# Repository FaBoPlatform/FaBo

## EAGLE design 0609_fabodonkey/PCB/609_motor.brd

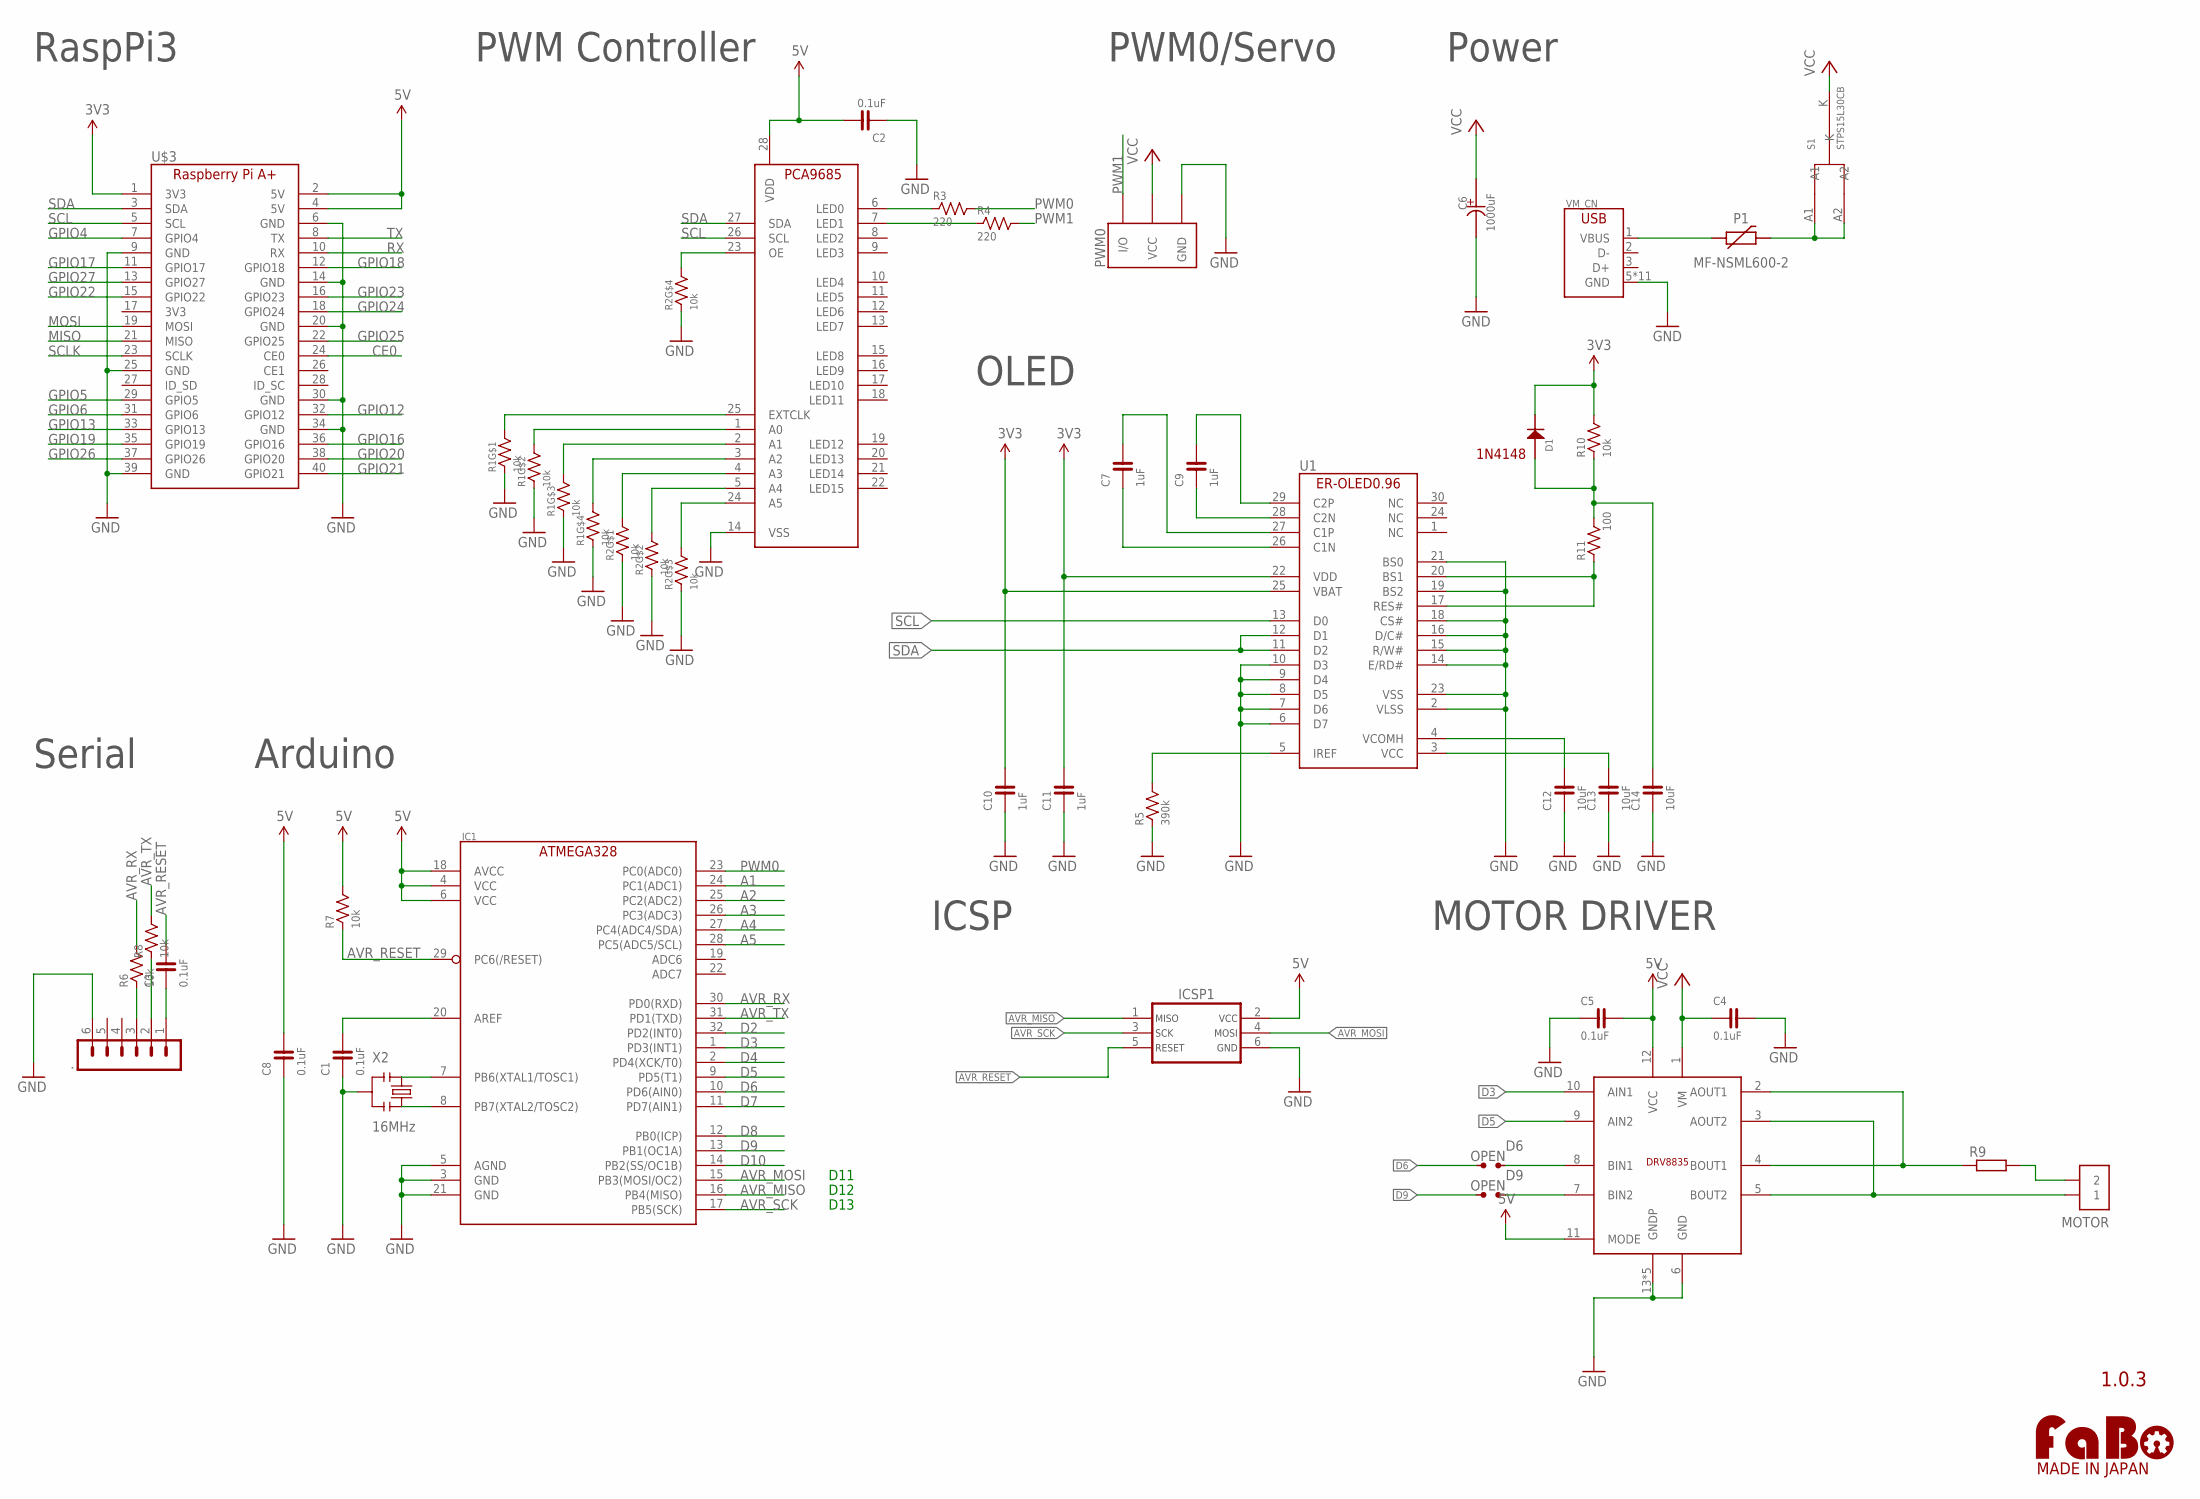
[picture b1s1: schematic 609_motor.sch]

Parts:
.: MA06-1
C1, C2, C3, C4, C5, C8: 0.1uF; 0603
C6: 1000uF; D12.5
C7, C9, C10, C11: 1uF; 0603
C12, C13, C14: 10uF; 0603
D1: 1N4148; 1N4148W
D6, D9: OPEN; SMD-JUMPER-2-OPEN
IC1: ATMEGA328P-AU; TQFP-32
ICSP1: ICSP_AVR-TC_NOHOLE; TC2030
M1: DRV8835
MOTOR: PIN_HEADER_1X2WIDE-WIDTH; PIN_1X2_WIDE_WIDTH
P1: MF-NSML600-2; 1206
PWM0: FABO_BRICK_3PIN-HEADER; FABO_BRICK_3PIN_HEADER
R1, R2: 10k; EXBV8V
R3, R4: 220; 0603
R5: 390k; 0603
R6, R7, R8, R10: 10k; 0603
R9: R-EU_0922/22; 0922/22
R11: 100; 0603
S1: STPS15L30CB; STPS15L30C
U1: ER-OLED0.96-1ER-CON30HT-1; ER-CON30HT-1
U$3: RASPBERRY_PI_A+
U$9: PCA9685
U$14: LOGO_FABO-M; LOGO_FABO_MS
VM_CN: USB-ZX62D; ZX62D-B-5PA8
X2: 16MHz; CSTNE_V_C

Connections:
3V3: C10.2, C11.2, D1.CATHODE, R10.2, U1.22 (VDD), U1.25 (VBAT), U$3.1 (3V3)
5V: C2.2, C5.2, C8.2, IC1.4 (VCC), IC1.6 (VCC), IC1.18 (AVCC), ICSP1.2, M1.11 (MODE), M1.12 (VCC), R7.2, U$3.2 (5V), U$3.4 (5V), U$9.28 (VDD)
A1: IC1.24 (PC1(ADC1))
A2: IC1.25 (PC2(ADC2))
A3: IC1.26 (PC3(ADC3))
A4: IC1.27 (PC4(ADC4/SDA))
A5: IC1.28 (PC5(ADC5/SCL))
AVR_MISO: IC1.16 (PB4(MISO)), ICSP1.1
AVR_MOSI: IC1.15 (PB3(MOSI/OC2)), ICSP1.4
AVR_RESET: C3.2, IC1.29 (PC6(/RESET)), ICSP1.5, R7.1
AVR_RX: IC1.30 (PD0(RXD)), R6.2
AVR_SCK: IC1.17 (PB5(SCK)), ICSP1.3
AVR_TX: IC1.31 (PD1(TXD)), R8.2
CE0: U$3.24 (CE0)
D2: IC1.32 (PD2(INT0))
D3: IC1.1 (PD3(INT1)), M1.10 (AIN1)
D4: IC1.2 (PD4(XCK/T0))
D5: IC1.9 (PD5(T1)), M1.9 (AIN2)
D6: D6.1, IC1.10 (PD6(AIN0))
D7: IC1.11 (PD7(AIN1))
D8: IC1.12 (PB0(ICP))
D9: D9.1, IC1.13 (PB1(OC1A))
D10: IC1.14 (PB2(SS/OC1B))
GND: ..6, C1.1, C2.1, C4.2, C5.1, C6.-, C8.1, C10.1, C11.1, C12.1, C13.1, C14.1, IC1.3 (GND), IC1.5 (AGND), IC1.21 (GND), ICSP1.6, M1.6 (GND), M1.13 (GNDP), M1.14 (GNDP), M1.15 (GNDP), M1.16 (GNDP), M1.17 (GNDP), PWM0.GND, R1.1, R1.2 (1), R1.3 (1), R1.4 (1), R2.1, R2.2 (1), R2.3 (1), R2.4 (1), R5.1, U1.2 (VLSS), U1.6 (D7), U1.7 (D6), U1.8 (D5), U1.9 (D4), U1.10 (D3), U1.14 (E/RD#), U1.15 (R/W#), U1.16 (D/C#), U1.18 (CS#), U1.19 (BS2), U1.21 (BS0), U1.23 (VSS), U$3.6 (GND), U$3.9 (GND), U$3.14 (GND), U$3.20 (GND), U$3.25 (GND), U$3.30 (GND), U$3.34 (GND), U$3.39 (GND), U$9.14 (VSS), VM_CN.5 (GND), VM_CN.B1 (GND), VM_CN.B2 (GND), VM_CN.B3 (GND), VM_CN.B4 (GND), VM_CN.T1 (GND), VM_CN.T2 (GND), VM_CN.T3 (GND), VM_CN.T4 (GND), VM_CN.T5 (GND), VM_CN.T6 (GND), X2.2
GPIO4: U$3.7 (GPIO4)
GPIO5: U$3.29 (GPIO5)
GPIO6: U$3.31 (GPIO6)
GPIO12: U$3.32 (GPIO12)
GPIO13: U$3.33 (GPIO13)
GPIO16: U$3.36 (GPIO16)
GPIO17: U$3.11 (GPIO17)
GPIO18: U$3.12 (GPIO18)
GPIO19: U$3.35 (GPIO19)
GPIO20: U$3.38 (GPIO20)
GPIO21: U$3.40 (GPIO21)
GPIO22: U$3.15 (GPIO22)
GPIO23: U$3.16 (GPIO23)
GPIO24: U$3.18 (GPIO24)
GPIO25: U$3.22 (GPIO25)
GPIO26: U$3.37 (GPIO26)
GPIO27: U$3.13 (GPIO27)
LED0: R3.1, U$9.6 (LED0)
LED1: R4.1, U$9.7 (LED1)
MISO: U$3.21 (MISO)
MOSI: U$3.19 (MOSI)
unnamed: C7.2, U1.27 (C1P)
unnamed: D6.2, M1.8 (BIN1)
unnamed: ..3, R6.1
unnamed: IC1.8 (PB7(XTAL2/TOSC2)), X2.3
unnamed: ..2, R8.1
unnamed: R2.5 (2), U$9.23 (OE)
unnamed: R1.8 (2), U$9.25 (EXTCLK)
unnamed: R1.7 (2), U$9.1 (A0)
unnamed: R1.6 (2), U$9.2 (A1)
unnamed: R1.5 (2), U$9.3 (A2)
unnamed: R2.8 (2), U$9.4 (A3)
unnamed: R2.7 (2), U$9.5 (A4)
unnamed: R2.6 (2), U$9.24 (A5)
unnamed: IC1.7 (PB6(XTAL1/TOSC1)), X2.1
unnamed: C1.2, IC1.20 (AREF)
unnamed: ..1, C3.1
unnamed: D9.2, M1.7 (BIN2)
unnamed: MOTOR.2, R9.2
unnamed: C7.1, U1.26 (C1N)
unnamed: M1.2 (AOUT1), M1.4 (BOUT1), R9.1
unnamed: M1.3 (AOUT2), M1.5 (BOUT2), MOTOR.1
unnamed: C9.1, U1.28 (C2N)
unnamed: C9.2, U1.29 (C2P)
unnamed: R5.2, U1.5 (IREF)
unnamed: C12.2, U1.4 (VCOMH)
unnamed: C13.2, U1.3 (VCC)
unnamed: R11.1, U1.17 (RES#), U1.20 (BS1)
unnamed: C14.2, D1.ANODE, R10.1, R11.2
PTCP1: P1.P$1 (1), VM_CN.1 (VBUS)
PTCP2: P1.P$2 (2), S1.A1, S1.A2
PWM0: IC1.23 (PC0(ADC0)), R3.2
PWM1: PWM0.I/O, R4.2
RX: U$3.10 (RX)
SCL: U1.13 (D0), U$3.5 (SCL), U$9.26 (SCL)
SCLK: U$3.23 (SCLK)
SDA: U1.11 (D2), U1.12 (D1), U$3.3 (SDA), U$9.27 (SDA)
TX: U$3.8 (TX)
VCC: C4.1, C6.+, M1.1 (VM), PWM0.VCC, S1.K

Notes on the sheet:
PWM0/Servo
1.0.3
RaspPi3
PWM Controller
D11
D12
D13
Arduino
Power
ICSP
MOTOR DRIVER
Serial
1N4148
OLED

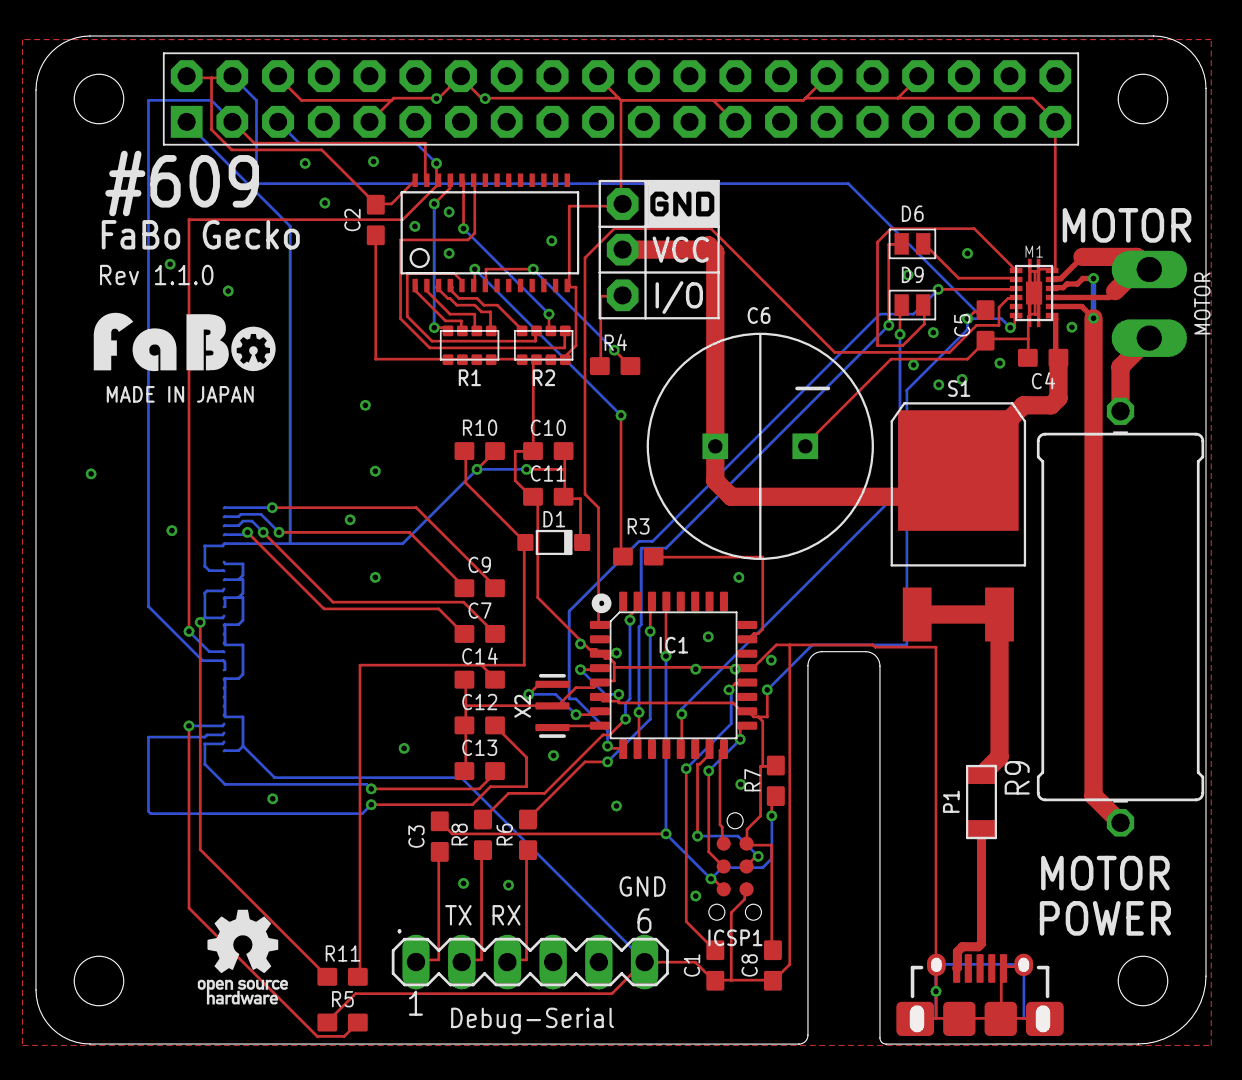
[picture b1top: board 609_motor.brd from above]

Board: 2 copper layers, 65.0 x 56.0 mm, 44 parts (0 on the bottom side), 50 nets.

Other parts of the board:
U$4: LOGO_OSHW_T_MS
U$7: LOGO_SILK_GND

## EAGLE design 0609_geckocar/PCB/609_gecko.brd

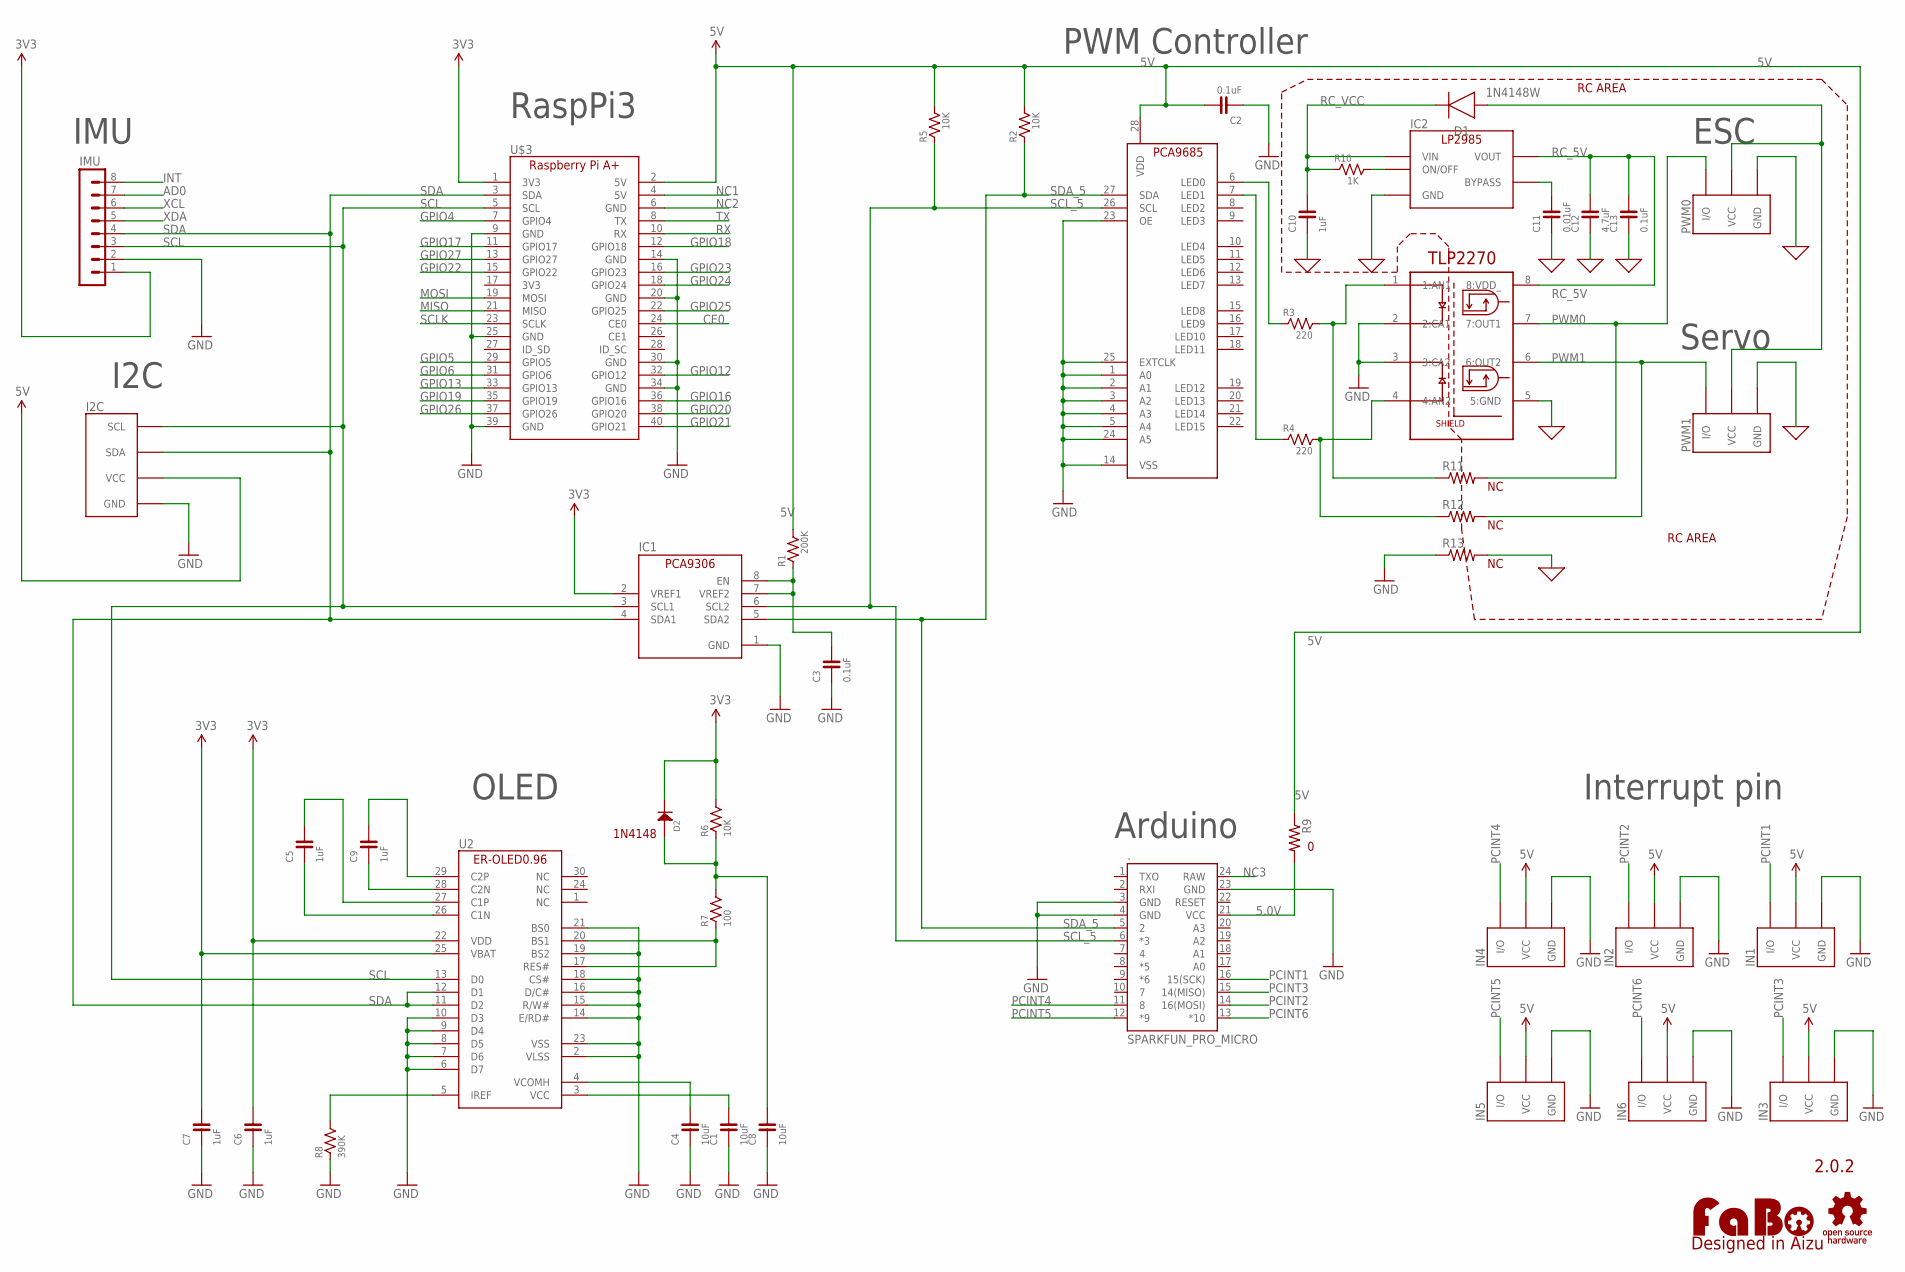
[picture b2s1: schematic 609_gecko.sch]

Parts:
.: SPARKFUN_PRO_MICRO
C1, C4, C8: 10uF; 0603
C2, C3, C13: 0.1uF; 0603
C5, C6, C7, C9, C10: 1uF; 0603
C11: 0.01uF; 0603
C12: 4.7uF; 0603
D1: 1N4148W; SOD3715X135
D2: 1N4148; 1N4148W
I2C: FABO_BRICK_I2C-B04B-PASK-1_SILK; FABO_BRICK_I2C_B04B-PASK-1_SILK
IC1: PCA9306_SSOP; 8PIN-SSOP
IC2: LP2985-33DBV; SOT-23-5
IMU: MA08-1
IN1, IN2, IN3, IN4, IN5, IN6: FABO_BRICK_3PIN-HEADER; FABO_BRICK_3PIN_HEADER
LOGO1: LOGO_FABO-M; LOGO_FABO_M
PWM0, PWM1: FABO_BRICK_3PIN-HEADER; FABO_BRICK_3PIN_HEADER
R1: 200K; 0603
R2, R5, R6: 10K; 0603
R3, R4: 220; 0603
R7: 100; 0603
R8: 390K; 0603
R9, R11, R12, R13: CRCW08050000Z0EA; RES_0805
R10: 1K; 0603
U2: ER-OLED0.96-1ER-CON30HT-1; ER-CON30HT-1
U$3: RASPBERRY_PI_A+
U$9: PCA9685
U$10: TLP2270
U$12: LOGO_OSHW-M_BOTTOM; LOGO_OSHW_M_BOTTOM

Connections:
0: C10.1, C11.1, C12.1, C13.1, IC2.2 (GND), PWM0.GND, PWM1.GND, R13.2, U$10.5 (5:GND)
3V3: C6.2, C7.2, D2.CATHODE, IC1.2 (VREF1), IMU.1, R6.2, U2.22 (VDD), U2.25 (VBAT), U$3.1 (3V3)
5.0V: ..21 (VCC), R9.2
5V: C2.2, I2C.VCC, IN1.VCC, IN2.VCC, IN3.VCC, IN4.VCC, IN5.VCC, IN6.VCC, R1.2, R2.2, R5.2, R9.1, U$3.2 (5V), U$9.28 (VDD)
AD0: IMU.7
CE0: U$3.24 (CE0)
GND: ..3 (GND), ..4 (GND), ..23 (GND), C1.1, C2.1, C3.1, C4.1, C6.1, C7.1, C8.1, I2C.GND, IC1.1 (GND), IMU.2, IN1.GND, IN2.GND, IN3.GND, IN4.GND, IN5.GND, IN6.GND, R8.1, R13.1, U2.2 (VLSS), U2.6 (D7), U2.7 (D6), U2.8 (D5), U2.9 (D4), U2.10 (D3), U2.14 (E/RD#), U2.15 (R/W#), U2.16 (D/C#), U2.18 (CS#), U2.19 (BS2), U2.21 (BS0), U2.23 (VSS), U$3.9 (GND), U$3.14 (GND), U$3.20 (GND), U$3.25 (GND), U$3.30 (GND), U$3.34 (GND), U$3.39 (GND), U$9.1 (A0), U$9.2 (A1), U$9.3 (A2), U$9.4 (A3), U$9.5 (A4), U$9.14 (VSS), U$9.23 (OE), U$9.24 (A5), U$9.25 (EXTCLK), U$10.2 (2:CA1), U$10.3 (3:CA2)
GPIO4: U$3.7 (GPIO4)
GPIO5: U$3.29 (GPIO5)
GPIO6: U$3.31 (GPIO6)
GPIO12: U$3.32 (GPIO12)
GPIO13: U$3.33 (GPIO13)
GPIO16: U$3.36 (GPIO16)
GPIO17: U$3.11 (GPIO17)
GPIO18: U$3.12 (GPIO18)
GPIO19: U$3.35 (GPIO19)
GPIO20: U$3.38 (GPIO20)
GPIO21: U$3.40 (GPIO21)
GPIO22: U$3.15 (GPIO22)
GPIO23: U$3.16 (GPIO23)
GPIO24: U$3.18 (GPIO24)
GPIO25: U$3.22 (GPIO25)
GPIO26: U$3.37 (GPIO26)
GPIO27: U$3.13 (GPIO27)
INT: IMU.8
MISO: U$3.21 (MISO)
MOSI: U$3.19 (MOSI)
unnamed: R3.1, U$9.6 (LED0)
unnamed: C5.2, U2.27 (C1P)
unnamed: R4.1, U$9.7 (LED1)
unnamed: C3.2, IC1.7 (VREF2), IC1.8 (EN), R1.1
unnamed: D1.2 (A), PWM0.VCC, PWM1.VCC
unnamed: R3.2, R11.1, U$10.1 (1:AN1)
unnamed: R4.2, R12.1, U$10.4 (4:AN2)
unnamed: IC2.3 (ON/OFF), R10.2
unnamed: C11.2, IC2.4 (BYPASS)
unnamed: C5.1, U2.26 (C1N)
unnamed: C9.1, U2.28 (C2N)
unnamed: C9.2, U2.29 (C2P)
unnamed: R8.2, U2.5 (IREF)
unnamed: C4.2, U2.4 (VCOMH)
unnamed: C1.2, U2.3 (VCC)
unnamed: R7.1, U2.17 (RES#), U2.20 (BS1)
unnamed: C8.2, D2.ANODE, R6.1, R7.2
NC1: U$3.4 (5V)
NC2: U$3.6 (GND)
NC3: ..24 (RAW)
PCINT1: ..16 (15(SCK)), IN1.I/O
PCINT2: ..14 (16(MOSI)), IN2.I/O
PCINT3: ..15 (14(MISO)), IN3.I/O
PCINT4: ..11 (8), IN4.I/O
PCINT5: ..12 (*9), IN5.I/O
PCINT6: ..13 (*10), IN6.I/O
PWM0: PWM0.I/O, R11.2, U$10.7 (7:OUT1)
PWM1: PWM1.I/O, R12.2, U$10.6 (6:OUT2)
RC_5V: C12.2, C13.2, IC2.5 (VOUT), U$10.8 (8:VDD_)
RC_VCC: C10.2, D1.1 (C), IC2.1 (VIN), R10.1
RX: U$3.10 (RX)
SCL: I2C.SCL, IC1.3 (SCL1), IMU.3, U2.13 (D0), U$3.5 (SCL)
SCLK: U$3.23 (SCLK)
SCL_5: ..6 (*3), IC1.6 (SCL2), R5.1, U$9.26 (SCL)
SDA: I2C.SDA, IC1.4 (SDA1), IMU.4, U2.11 (D2), U2.12 (D1), U$3.3 (SDA)
SDA_5: ..5 (2), IC1.5 (SDA2), R2.1, U$9.27 (SDA)
TX: U$3.8 (TX)
XCL: IMU.6
XDA: IMU.5

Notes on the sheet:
ESC
2.0.2
RaspPi3
PWM Controller
Arduino
OLED
1N4148
I2C
IMU
Interrupt pin
Servo
RC AREA

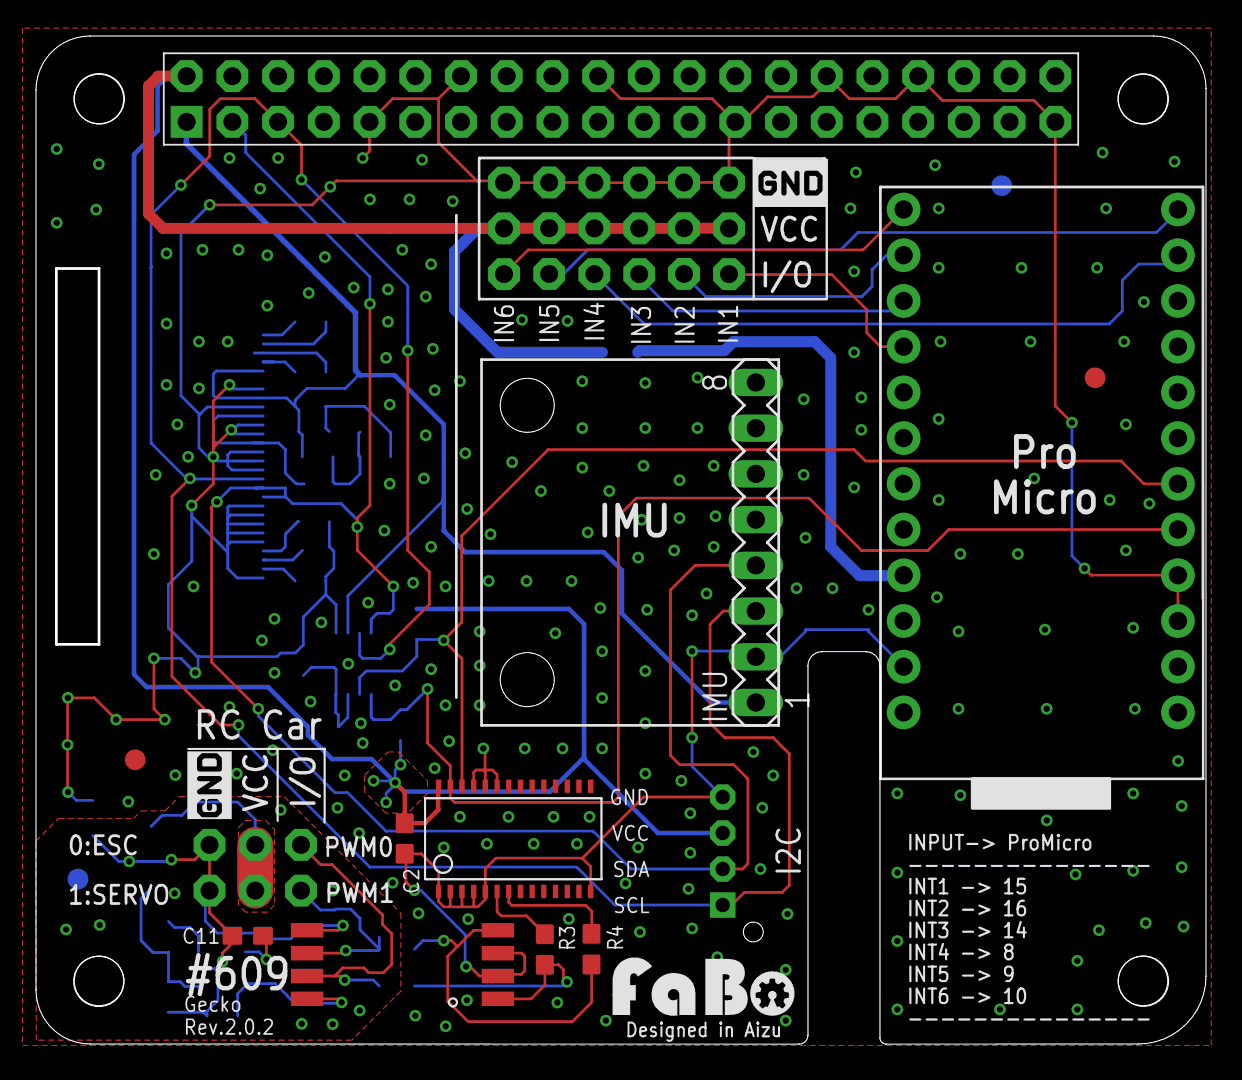
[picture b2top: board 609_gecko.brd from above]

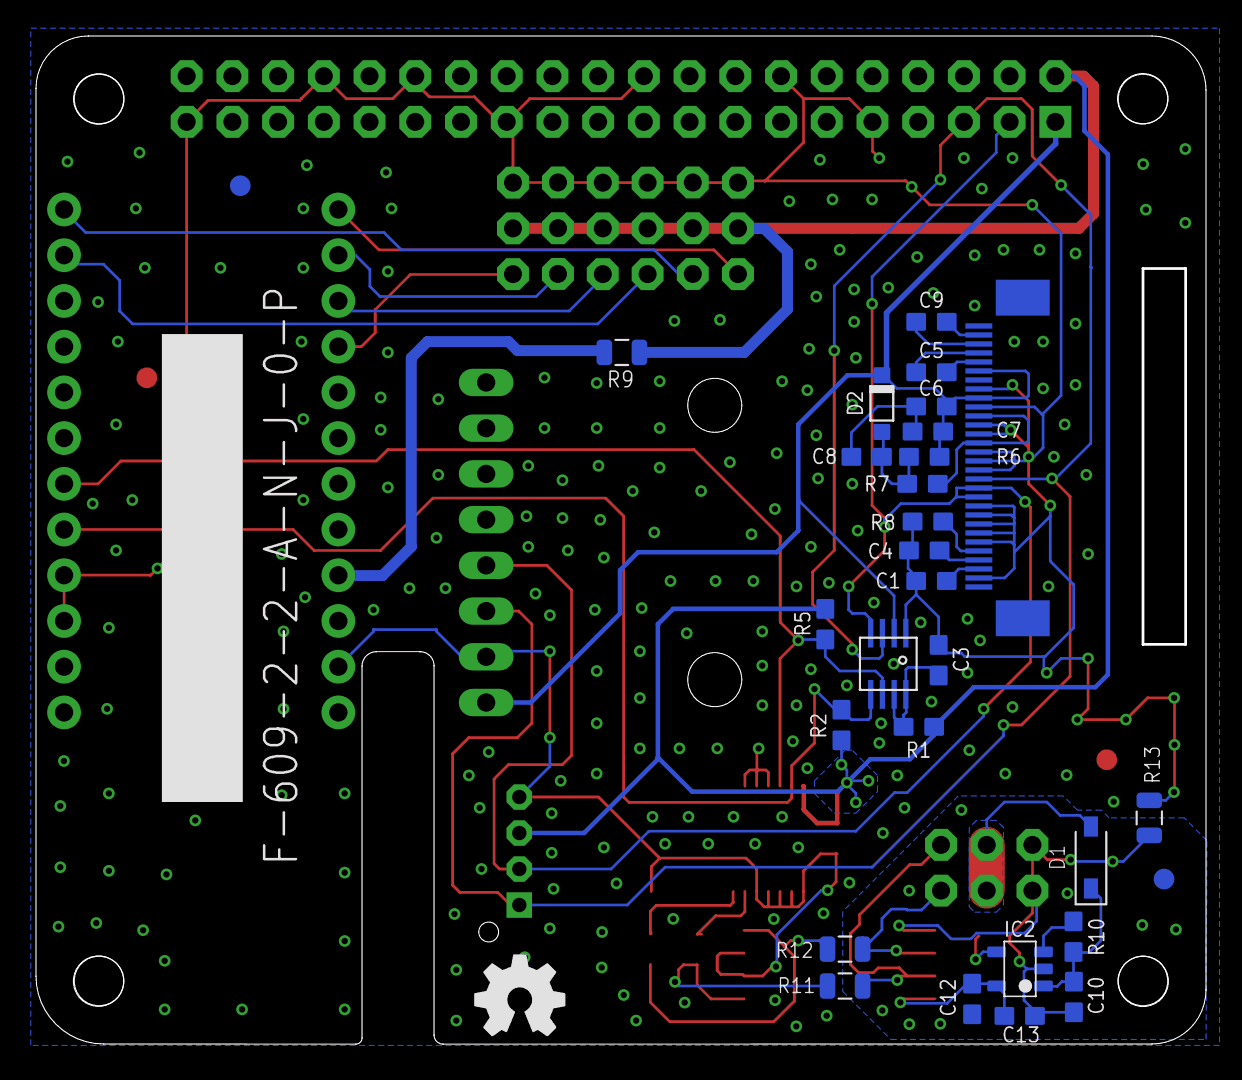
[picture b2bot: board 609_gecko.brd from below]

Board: 2 copper layers, 65.0 x 56.0 mm, 53 parts (28 on the bottom side), 36 nets.

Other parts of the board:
U$2, U$7: LOGO_SILK_GND
U$5, U$6, U$8, U$11: MARK_POINT_3MM

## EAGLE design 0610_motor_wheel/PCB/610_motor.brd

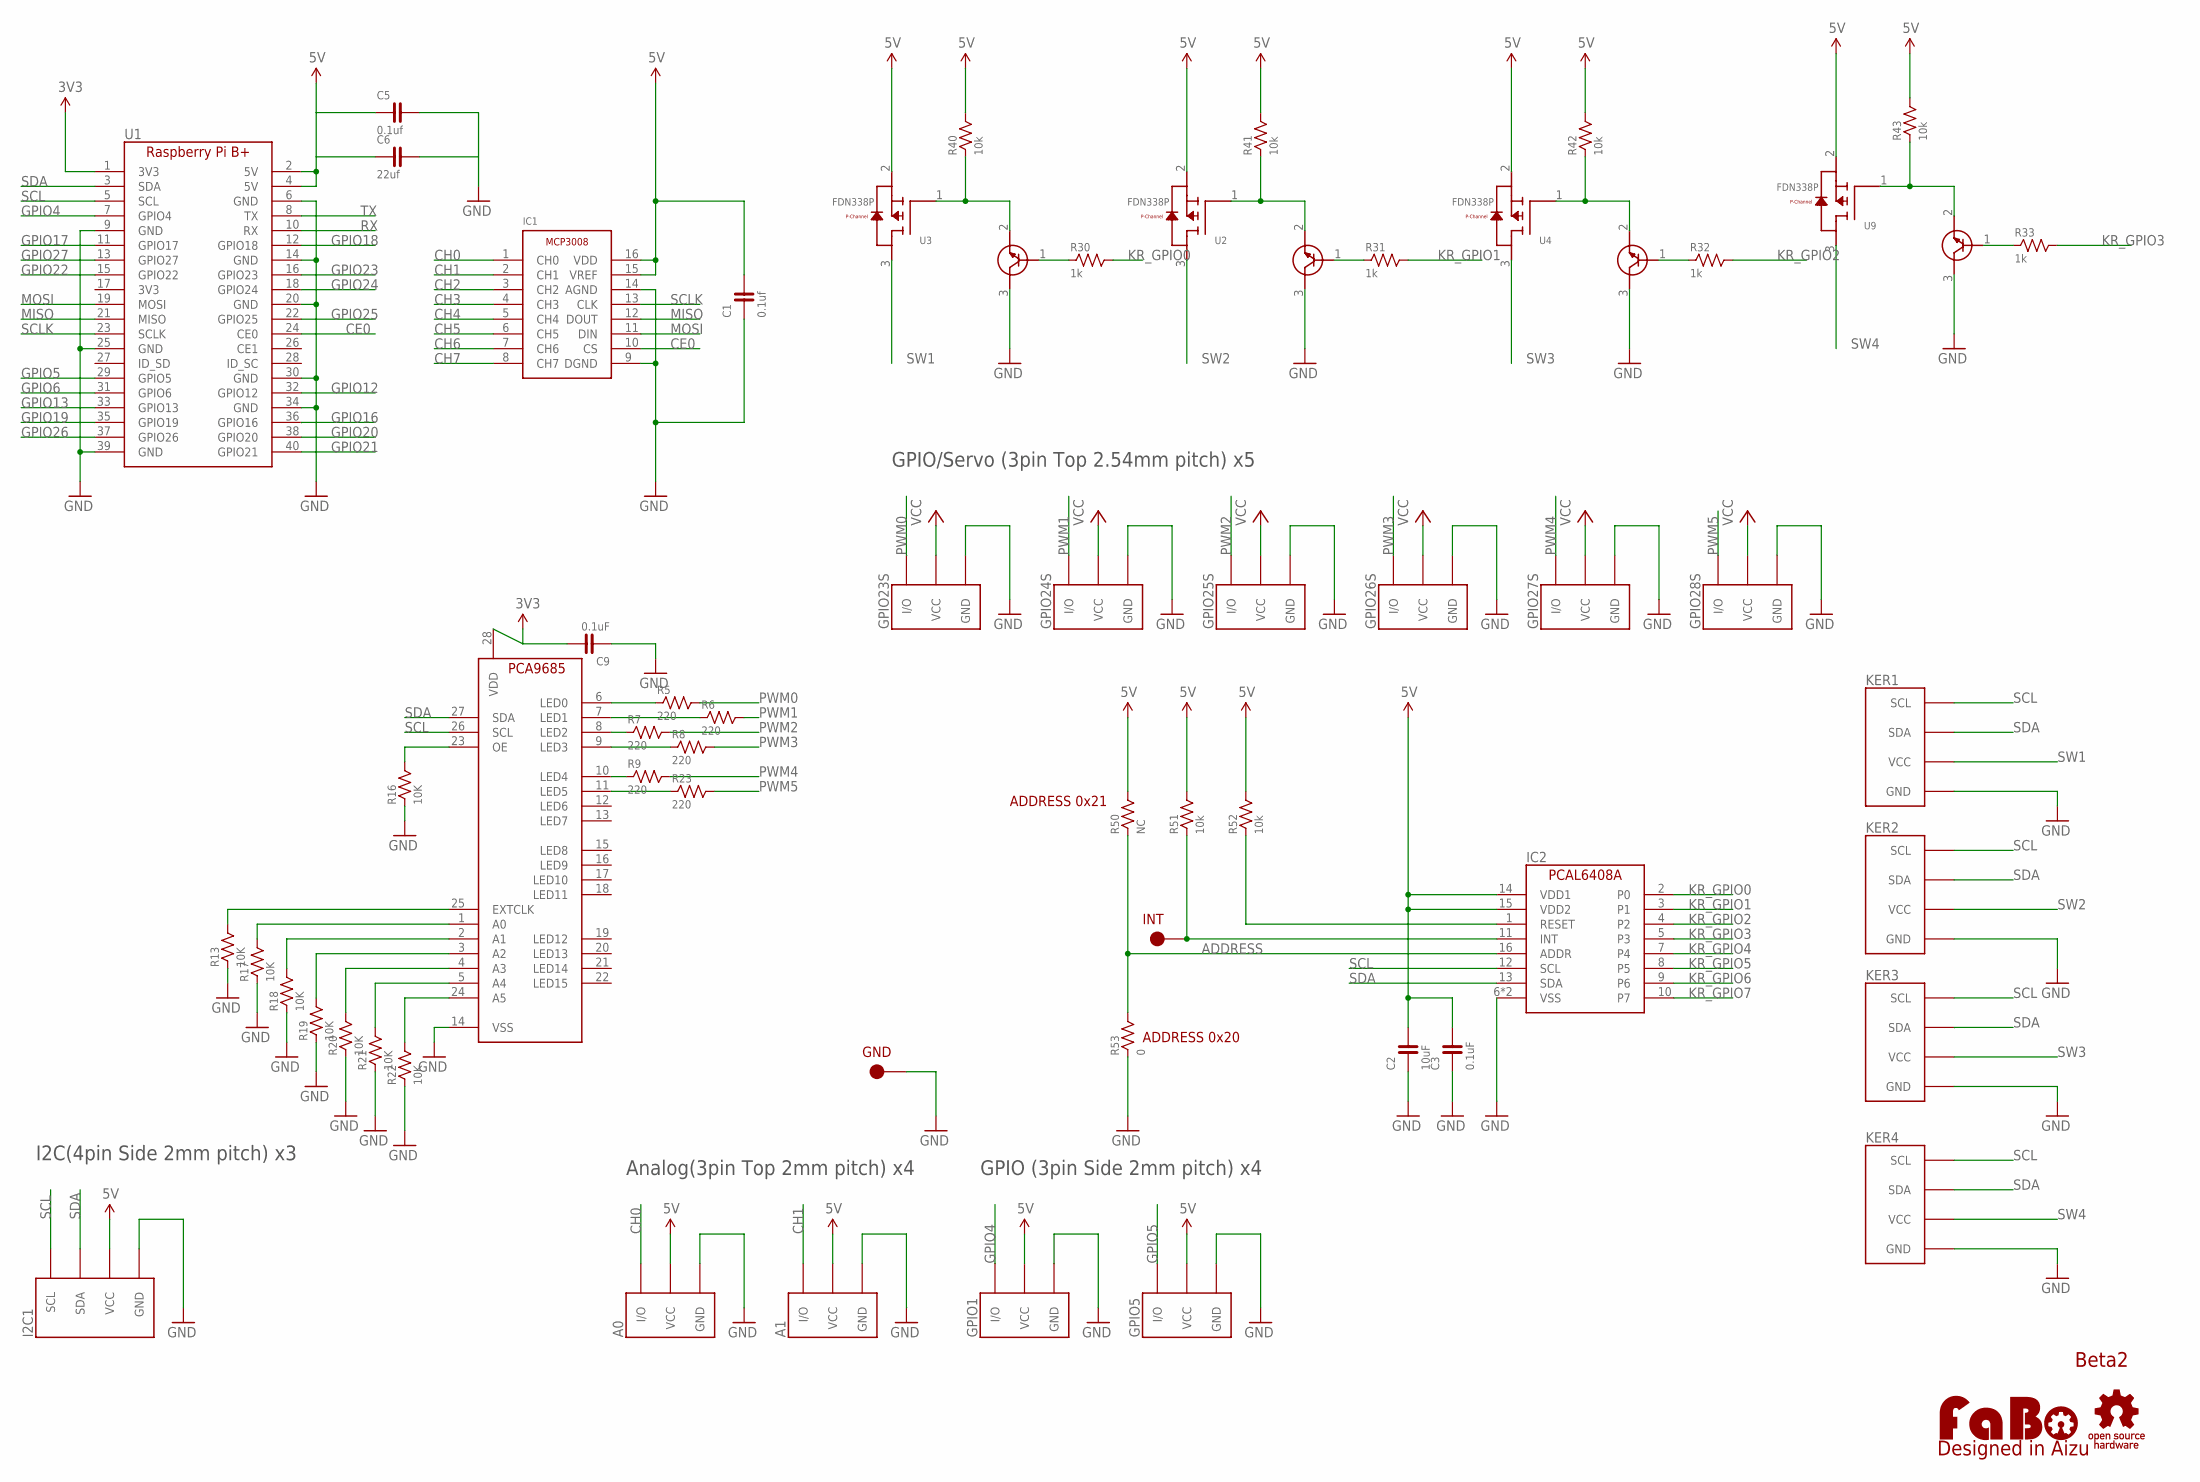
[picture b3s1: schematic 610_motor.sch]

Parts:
A0, A1: FABO_BRICK_3PIN-B03B-PASK-1; FABO_BRICK_3PIN_B03B-PASK-1
C1, C5: 0.1uf; 0603
C2: 10uF; 0603
C3, C9: 0.1uF; 0603
C6: 22uf; 0603
GPIO1, GPIO5: FABO_BRICK_3PIN-B03B-PASK-1; FABO_BRICK_3PIN_B03B-PASK-1
GPIO23S, GPIO24S, GPIO25S, GPIO26S, GPIO27S, GPIO28S: FABO_BRICK_3PIN-HEADER; FABO_BRICK_3PIN_HEADER
I2C1: FABO_BRICK_I2C-S04B-PASK-2; FABO_BRICK_I2C_S04B-PASK-2
IC1: MICROCHIP-MCP3008
IC2: NX-PCAL6408A; NXP-PCAL6408A
KER1, KER2, KER3, KER4: FABO_BRICK_I2C-S04B-PASK-2; FABO_BRICK_I2C_S04B-PASK-2
LOGO1: LOGO_FABO-M; LOGO_FABO_M
R5, R6, R7, R8, R9, R23: 220; 0603
R13, R22: 10K; 0402
R16, R17, R18, R19, R20, R21: 10K; 0603
R30, R31, R32, R33: 1k; 0603-NARROW
R40, R41, R42, R43, R51, R52: 10k; 0603-NARROW
R50: NC; 0603-NARROW
R53: 0; 0603-NARROW
T1, T2, T3, T4: TRANSISTORMMBT2222; SOT-23
TP1, TP2: TP-15
U1: RASPBERRY_PI_B+
U2, U3, U4, U9: FDN338P; SOT-23
U$2: LOGO_OSHW-M_BOTTOM; LOGO_OSHW_M_BOTTOM
U$9: PCA9685

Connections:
3V3: C9.2, U1.1 (3V3), U$9.28 (VDD)
5V: A0.VCC, A1.VCC, C1.2, C2.2, C3.2, C5.1, C6.1, GPIO1.VCC, GPIO5.VCC, I2C1.VCC, IC1.15 (VREF), IC1.16 (VDD), IC2.14 (VDD1), IC2.15 (VDD2), R40.2, R41.2, R42.2, R43.2, R50.2, R51.2, R52.2, U1.2 (5V), U1.4 (5V), U2.2 (S), U3.2 (S), U4.2 (S), U9.2 (S)
ADDRESS: IC2.16 (ADDR), R50.1, R53.2
CE0: IC1.10 (CS), U1.24 (CE0)
CH0: A0.I/O, IC1.1 (CH0)
CH1: A1.I/O, IC1.2 (CH1)
CH2: IC1.3 (CH2)
CH3: IC1.4 (CH3)
CH4: IC1.5 (CH4)
CH5: IC1.6 (CH5)
CH6: IC1.7 (CH6)
CH7: IC1.8 (CH7)
GND: A0.GND, A1.GND, C1.1, C2.1, C3.1, C5.2, C6.2, C9.1, GPIO1.GND, GPIO5.GND, GPIO23S.GND, GPIO24S.GND, GPIO25S.GND, GPIO26S.GND, GPIO27S.GND, GPIO28S.GND, I2C1.GND, IC1.9 (DGND), IC1.14 (AGND), IC2.6 (VSS), IC2.17 (VSS), KER1.GND, KER2.GND, KER3.GND, KER4.GND, R13.P$1 (1), R16.1, R17.1, R18.1, R19.1, R20.1, R21.1, R22.P$1 (1), R53.1, T1.3 (C), T2.3 (C), T3.3 (C), T4.3 (C), TP2.1, U1.6 (GND), U1.9 (GND), U1.14 (GND), U1.20 (GND), U1.25 (GND), U1.30 (GND), U1.34 (GND), U1.39 (GND), U$9.14 (VSS)
GPIO4: GPIO1.I/O, U1.7 (GPIO4)
GPIO5: GPIO5.I/O, U1.29 (GPIO5)
GPIO6: U1.31 (GPIO6)
GPIO12: U1.32 (GPIO12)
GPIO13: U1.33 (GPIO13)
GPIO16: U1.36 (GPIO16)
GPIO17: U1.11 (GPIO17)
GPIO18: U1.12 (GPIO18)
GPIO19: U1.35 (GPIO19)
GPIO20: U1.38 (GPIO20)
GPIO21: U1.40 (GPIO21)
GPIO22: U1.15 (GPIO22)
GPIO23: U1.16 (GPIO23)
GPIO24: U1.18 (GPIO24)
GPIO25: U1.22 (GPIO25)
GPIO26: U1.37 (GPIO26)
GPIO27: U1.13 (GPIO27)
KR_GPIO0: IC2.2 (P0), R30.2
KR_GPIO1: IC2.3 (P1), R31.2
KR_GPIO2: IC2.4 (P2), R32.2
KR_GPIO3: IC2.5 (P3), R33.2
KR_GPIO4: IC2.7 (P4)
KR_GPIO5: IC2.8 (P5)
KR_GPIO6: IC2.9 (P6)
KR_GPIO7: IC2.10 (P7)
LED0: R5.1, U$9.6 (LED0)
LED1: R6.1, U$9.7 (LED1)
LED2: R7.1, U$9.8 (LED2)
LED3: R8.1, U$9.9 (LED3)
LED4: R9.1, U$9.10 (LED4)
LED5: R23.1, U$9.11 (LED5)
MISO: IC1.12 (DOUT), U1.21 (MISO)
MOSI: IC1.11 (DIN), U1.19 (MOSI)
unnamed: R31.1, T2.1 (B)
unnamed: IC2.11 (INT), R51.1, TP1.1
unnamed: R40.1, T1.2 (E), U3.1 (G)
unnamed: R41.1, T2.2 (E), U2.1 (G)
unnamed: R30.1, T1.1 (B)
unnamed: R16.2, U$9.23 (OE)
unnamed: R13.P$2 (2), U$9.25 (EXTCLK)
unnamed: R17.2, U$9.1 (A0)
unnamed: R18.2, U$9.2 (A1)
unnamed: R19.2, U$9.3 (A2)
unnamed: R20.2, U$9.4 (A3)
unnamed: R21.2, U$9.5 (A4)
unnamed: R22.P$2 (2), U$9.24 (A5)
unnamed: R42.1, T3.2 (E), U4.1 (G)
unnamed: R32.1, T3.1 (B)
unnamed: IC2.1 (RESET), R52.1
unnamed: R43.1, T4.2 (E), U9.1 (G)
unnamed: R33.1, T4.1 (B)
PWM0: GPIO23S.I/O, R5.2
PWM1: GPIO24S.I/O, R6.2
PWM2: GPIO25S.I/O, R7.2
PWM3: GPIO26S.I/O, R8.2
PWM4: GPIO27S.I/O, R9.2
PWM5: GPIO28S.I/O, R23.2
RX: U1.10 (RX)
SCL: I2C1.SCL, IC2.12 (SCL), KER1.SCL, KER2.SCL, KER3.SCL, KER4.SCL, U1.5 (SCL), U$9.26 (SCL)
SCLK: IC1.13 (CLK), U1.23 (SCLK)
SDA: I2C1.SDA, IC2.13 (SDA), KER1.SDA, KER2.SDA, KER3.SDA, KER4.SDA, U1.3 (SDA), U$9.27 (SDA)
SW1: KER1.VCC, U3.3 (D)
SW2: KER2.VCC, U2.3 (D)
SW3: KER3.VCC, U4.3 (D)
SW4: KER4.VCC, U9.3 (D)
TX: U1.8 (TX)
VCC: GPIO23S.VCC, GPIO24S.VCC, GPIO25S.VCC, GPIO26S.VCC, GPIO27S.VCC, GPIO28S.VCC

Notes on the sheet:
Beta2
GPIO (3pin Side 2mm pitch) x4
I2C(4pin Side 2mm pitch) x3
GPIO/Servo (3pin Top 2.54mm pitch) x5
Analog(3pin Top 2mm pitch) x4
INT
GND
ADDRESS 0x20
ADDRESS 0x21

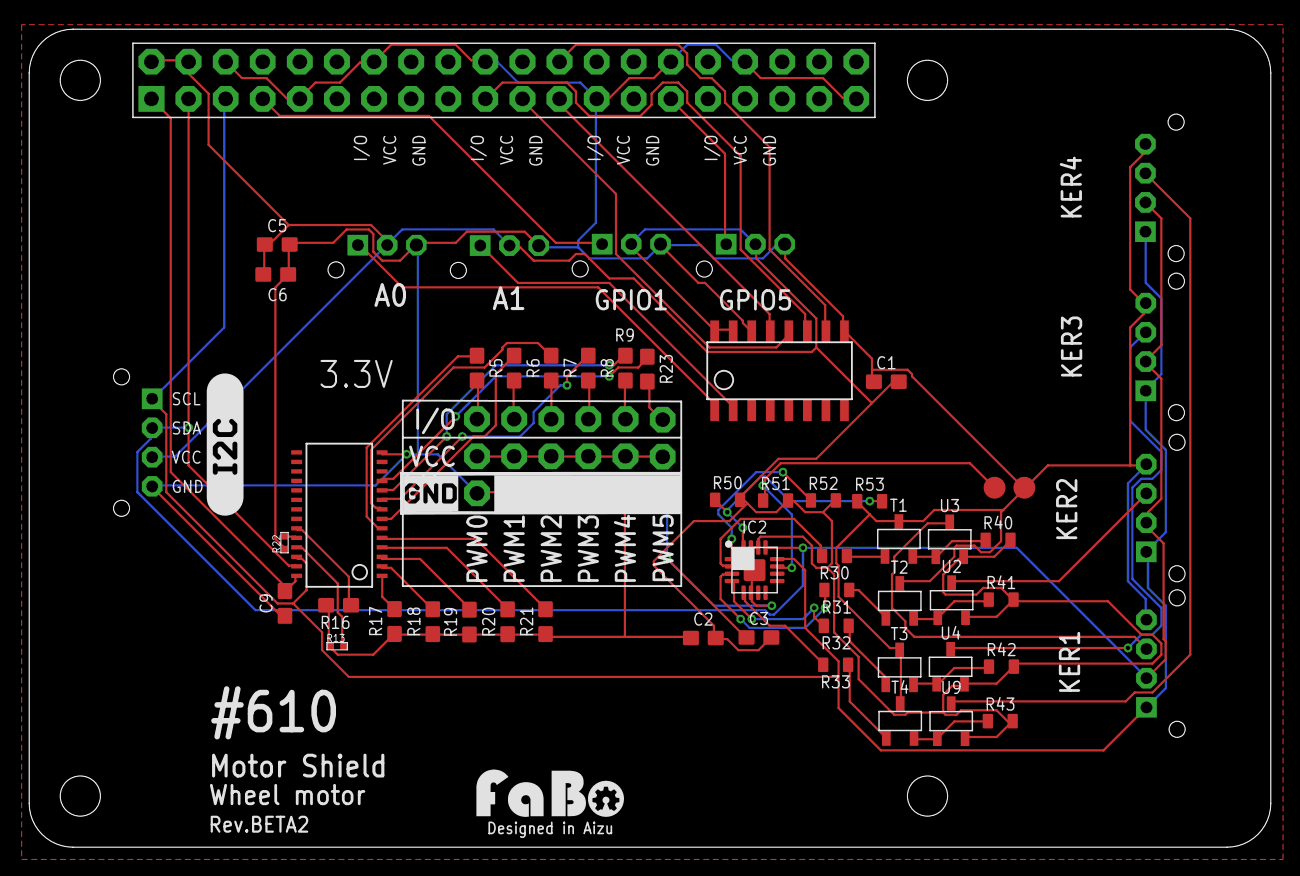
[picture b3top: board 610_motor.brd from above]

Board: 2 copper layers, 85.0 x 56.0 mm, 65 parts (0 on the bottom side), 53 nets.

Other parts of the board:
U$6: LOGO_SILK_I2C
U$7: LOGO_SILK_GND

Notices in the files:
parts and their libraries:
FaBo-etc: Released under the Creative Commons Attribution-ShareAlike 4.0 License
https://creativecommons.org/licenses/by-sa/4.0
FaBo-etc: Released under the Creative Commons
SparkFun-Boards: Licensing: Creative Commons ShareAlike 4.0 International - https://creativecommons.org/licenses/by-sa/4.0
